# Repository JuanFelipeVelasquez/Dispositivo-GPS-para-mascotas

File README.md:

# Sistema Integrado de GPS para mascotas

Integrantes:

* Juan Felipe Velásquez Jaramillo - juvelasquezj@unal.edu.co
* Wilmer Daniel Velásquez Tumay - wvelasquezt@unal.edu.co
* Juan Pablo Avendaño Acero - javendanoa@unal.edu.co

## Banner del proyecto

## Resumen
El objetivo principal de este proyecto académico es diseñar un dispositivo portátil de localización para mascotas que pueda ser colocado en su correa. Esta iniciativa surge en respuesta a la creciente preocupación de los propietarios por la seguridad de sus mascotas. Aunque los dueños desean evitar que sus mascotas se pierdan, no siempre pueden vigilarlas constantemente debido a diversas circunstancias. En tales casos, los animales pueden ser confiados a terceros o incluso quedarse solos por un tiempo determinado. Para abordar esta problemática, el proyecto propone el uso de una página web que permita a los dueños conocer la ubicación precisa y en tiempo real de sus mascotas. Esto se logrará mediante el desarrollo de un sistema de rastreo basado en GPS, utilizando módulos LORA para garantizar una amplia y eficiente cobertura. El dispositivo de localización diseñado permitirá a los propietarios supervisar la ubicación de sus mascotas en todo momento, brindando una mayor tranquilidad y seguridad. Además, la tecnología GPS y los módulos LORA ofrecerán una precisión óptima, asegurando que los dueños puedan localizar a sus mascotas incluso en áreas extensas. En conclusión, este proyecto académico busca desarrollar un dispositivo portátil de localización para mascotas que se integre con una página web, brindando a los propietarios la capacidad de conocer la ubicación exacta de sus animales en tiempo real. El uso de módulos LORA y la tecnología GPS garantizarán un rastreo preciso y una cobertura amplia, proporcionando a los dueños mayor tranquilidad y confianza en la seguridad de sus mascotas.

## Problematica
El motivo de la creación de este proyecto es que actualmente la seguridad se ha convertido en un factor de interés general entre los dueños de mascotas cuando se trata de que estas no se pierdan, sin embargo, por varios motivos los dueños no pueden estar todo el tiempo al pendiente de sus mascotas por lo que los dejan al cuidado de terceros o inclusive los dejan solos si así lo ameritan las circunstancias, por ello, este proyecto plantea que mediante una página web los padres puedan conocer en tiempo real y con alta precisión la ubicación de sus mascotas.

## Alcance
El proyecto define su alcance en esta primera etapa con la intercomunicación de los modulos lora y la integración del gps a los mismos

## Costos

## Objetivos

* Objetivo Principal
  
        Diseñar un dispositivo portátil de localización para mascotas que se pueda colocar en su correa.

* Objetivos Secundarios:

     1. Desarrollar un sistema de rastreo basado en GPS que permita conocer la ubicación precisa y en tiempo real de las mascotas.
     2.  Utilizar módulos LORA para garantizar una amplia y eficiente cobertura en el rastreo de las mascotas.
     3. Integrar el dispositivo de localización con una página web o mensaje de texto que brinde a los propietarios la capacidad de supervisar la ubicación exacta de sus mascotas en todo momento.
   
## Impactos

## Diagrama de flujo solución

## Diagrama de caja negra (no tecnologico)

## Diagrama de caja negra tecnológico

## Imagen proceso trabajo en tablero

## Esquematico pcb

## Pruebas/Imágenes
1. Imágen referencia para el proyecto.

2. Versión alternativa con modulo gms.

3. Versión preliminar.

## Conclusiones
* La utilización de módulos LORA aumenta el rango de
efectividad del GPS.
* La utilización de un GPS para las mascotas genera
mayor seguridad a los dueños de los mismos.
* La conección entre modulos lora se facilita al tener microprocesadores iguales en ambos sistemas.

## Video del proyecto.
[Video proyecto]()

## Referencias.
[Enlace Referencias](https://docs.google.com/document/d/1pl94NhDiLS5le3mnF0FaL84PyjT1eD7dEBsACEJOMd0/edit?usp=sharing)

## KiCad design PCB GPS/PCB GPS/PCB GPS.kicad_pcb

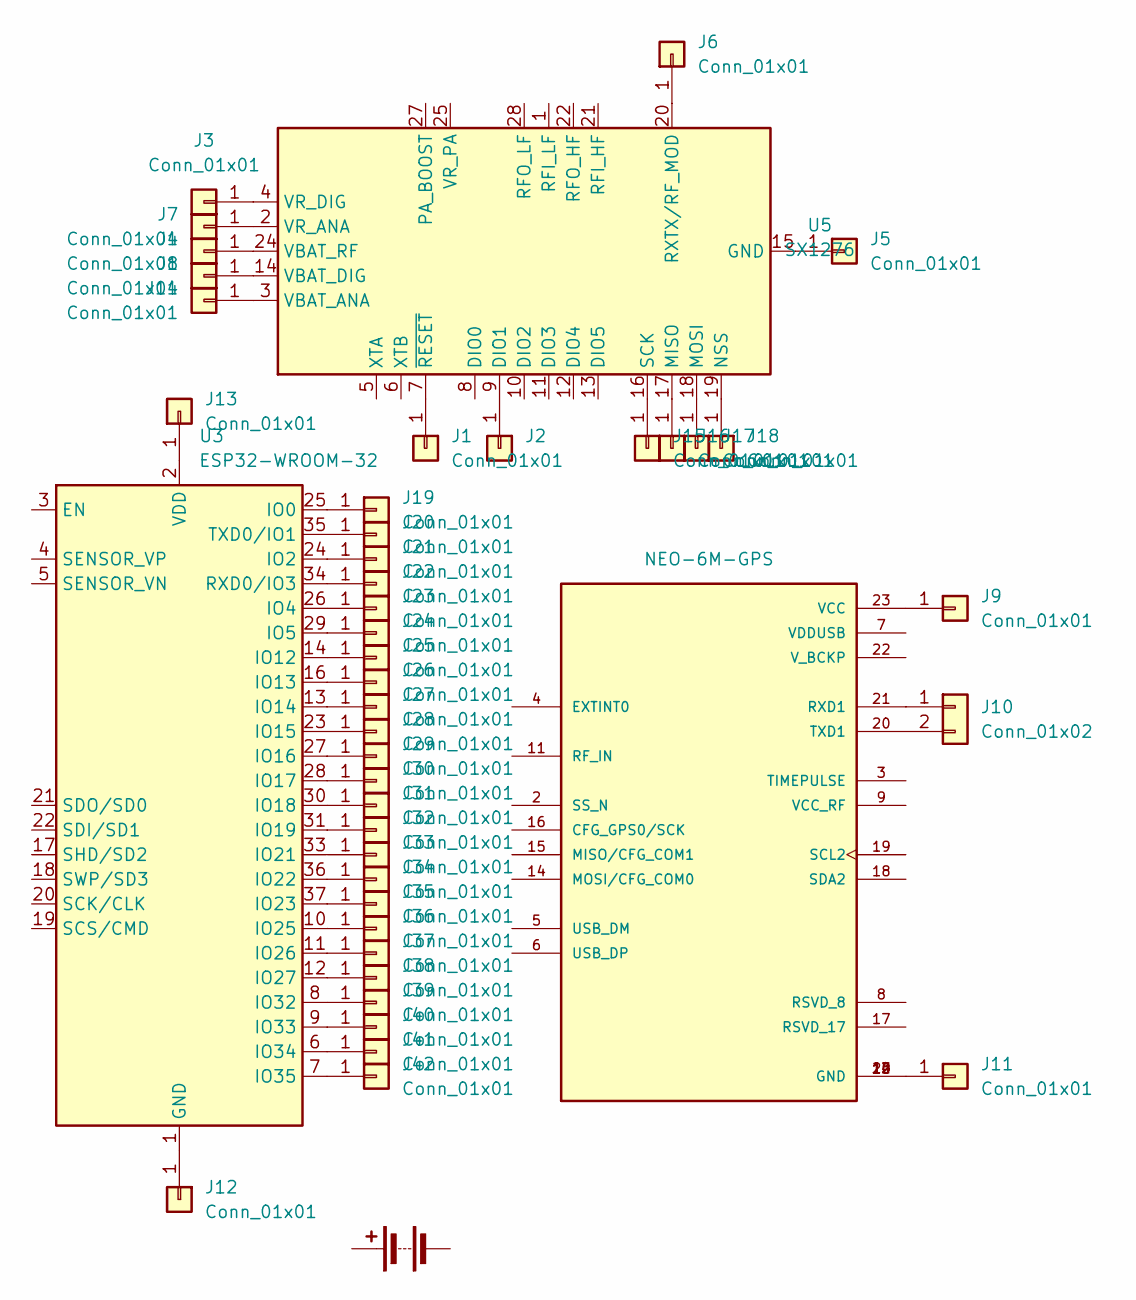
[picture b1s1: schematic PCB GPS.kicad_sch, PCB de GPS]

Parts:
BT1: Battery; BatteryHolder_Keystone_106_1x20mm
J1, J2: Conn_01x01; PinHeader_1x01_P2.54mm_Vertical
J3, J4, J5, J6, J7, J8, J9, J11, J12, J13, J14, J15, J16, J17, J18, J19, J20, J21, J22, J23, J24, J25, J26, J27, J28, J29, J30, J31, J32, J33, J34, J35, J36, J37, J38, J39, J40, J41, J42: Conn_01x01; PinHeader_1x01_P2.54mm_Horizontal
J10: Conn_01x02; PinHeader_1x02_P2.54mm_Horizontal
U3: ESP32-WROOM-32
U4: NEO-6M-GPS; ublox_NEO; PARTREV R15
U5: SX1276; QFN-28-1EP_6x6mm_P0.65mm_EP4.8x4.8mm

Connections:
unnamed: J1.1, U5.7 (~RESET)
unnamed: J2.1, U5.9 (DIO1)
unnamed: J3.1, U5.4 (VR_DIG)
unnamed: J4.1, U5.24 (VBAT_RF)
unnamed: J5.1, U5.15 (GND), U5.23 (GND), U5.26 (GND), U5.29 (GND)
unnamed: J6.1, U5.20 (RXTX/RF_MOD)
unnamed: J7.1, U5.2 (VR_ANA)
unnamed: J8.1, U5.14 (VBAT_DIG)
unnamed: J9.1, U4.23 (VCC)
unnamed: J10.1, U4.21 (RXD1)
unnamed: J10.2, U4.20 (TXD1)
unnamed: J11.1, U4.10 (GND), U4.12 (GND), U4.13 (GND), U4.24 (GND)
unnamed: J12.1, U3.1 (GND), U3.15 (GND), U3.38 (GND), U3.39 (GND)
unnamed: J13.1, U3.2 (VDD)
unnamed: J14.1, U5.3 (VBAT_ANA)
unnamed: J15.1, U5.16 (SCK)
unnamed: J16.1, U5.17 (MISO)
unnamed: J17.1, U5.18 (MOSI)
unnamed: J18.1, U5.19 (NSS)
unnamed: J19.1, U3.25 (IO0)
unnamed: J20.1, U3.35 (TXD0/IO1)
unnamed: J21.1, U3.24 (IO2)
unnamed: J22.1, U3.34 (RXD0/IO3)
unnamed: J23.1, U3.26 (IO4)
unnamed: J24.1, U3.29 (IO5)
unnamed: J25.1, U3.14 (IO12)
unnamed: J26.1, U3.16 (IO13)
unnamed: J27.1, U3.13 (IO14)
unnamed: J28.1, U3.23 (IO15)
unnamed: J29.1, U3.27 (IO16)
unnamed: J30.1, U3.28 (IO17)
unnamed: J31.1, U3.30 (IO18)
unnamed: J32.1, U3.31 (IO19)
unnamed: J33.1, U3.33 (IO21)
unnamed: J34.1, U3.36 (IO22)
unnamed: J35.1, U3.37 (IO23)
unnamed: J36.1, U3.10 (IO25)
unnamed: J37.1, U3.11 (IO26)
unnamed: J38.1, U3.12 (IO27)
unnamed: J39.1, U3.8 (IO32)
unnamed: J40.1, U3.9 (IO33)
unnamed: J41.1, U3.6 (IO34)
unnamed: J42.1, U3.7 (IO35)

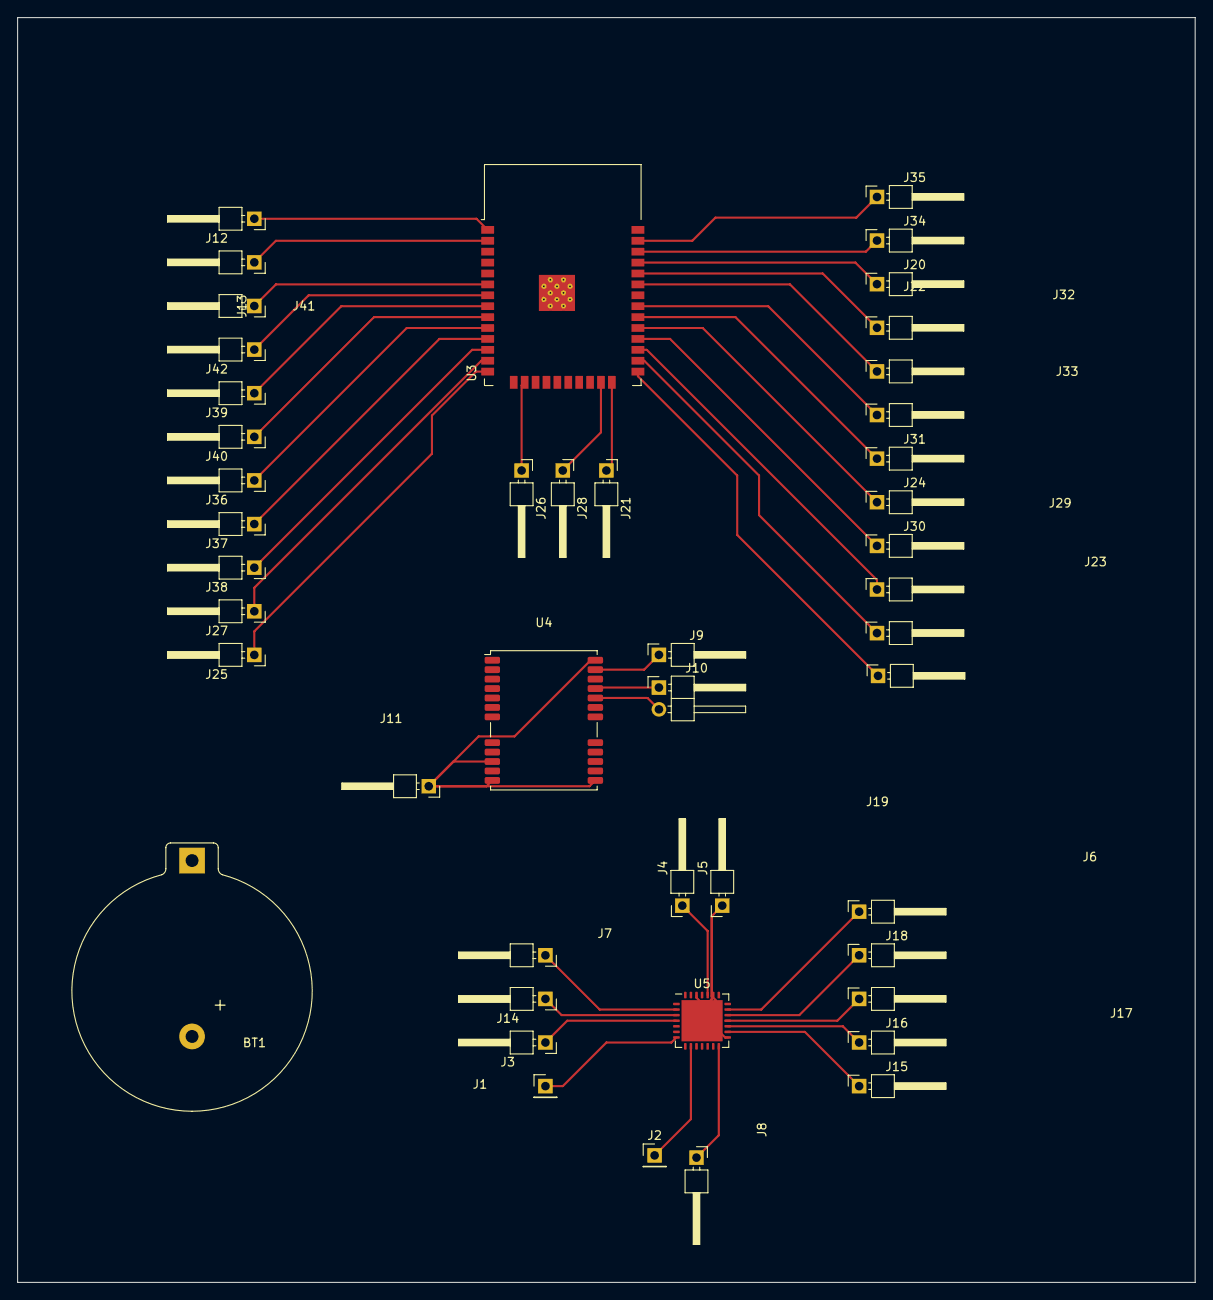
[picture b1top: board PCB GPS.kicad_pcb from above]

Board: 2 copper layers, 137.2 x 147.3 mm, 46 parts (0 on the bottom side), 43 nets.

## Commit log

2023-06-26 Creación de PCB para el proyecto
2023-06-26 README iniciado
2023-06-26 Modificación del README
2023-06-28 Readme.final
